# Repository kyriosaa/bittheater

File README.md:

# BitTheater: A Miniature Animation Showcase

BitTheater is a compact, tactile device that brings your custom animations to life, displaying up to 4 unique animations in a sleek, pocket-sized design.

Special thanks to [PCBWay](https://www.pcbway.com/) for their sponsorship and high-quality PCB prototyping service! Their PCBs are very high quality with many options to choose from and I got my order shipped to me within 3 days. Check them out if you want a custom PCB for your own project.

🎥 Demo Videos 🎥
- [Prototype](https://youtu.be/qVx4EneCoxs)
- [v1.0 PCB](https://youtu.be/kq-y1wTctfI)

## Features

- **Custom Animations -** Includes up to 4 custom animations on a 16x2 LCD screen
- **Tactile Controls -** Uses two tactile push buttons for a satisfying click on every button press
- **Compact Design -** The device is built on a small perfboard, allowing components to be neatly soldered for a compact and pocket-sized design.

## Hardware Components

- **Arduino Nano -** Microcontroller
- **SC162A3 -** 16x2 LCD Display
- **Push Buttons -** Buttons
- **220Ω Resistors -** Pull-down resistors for push buttons

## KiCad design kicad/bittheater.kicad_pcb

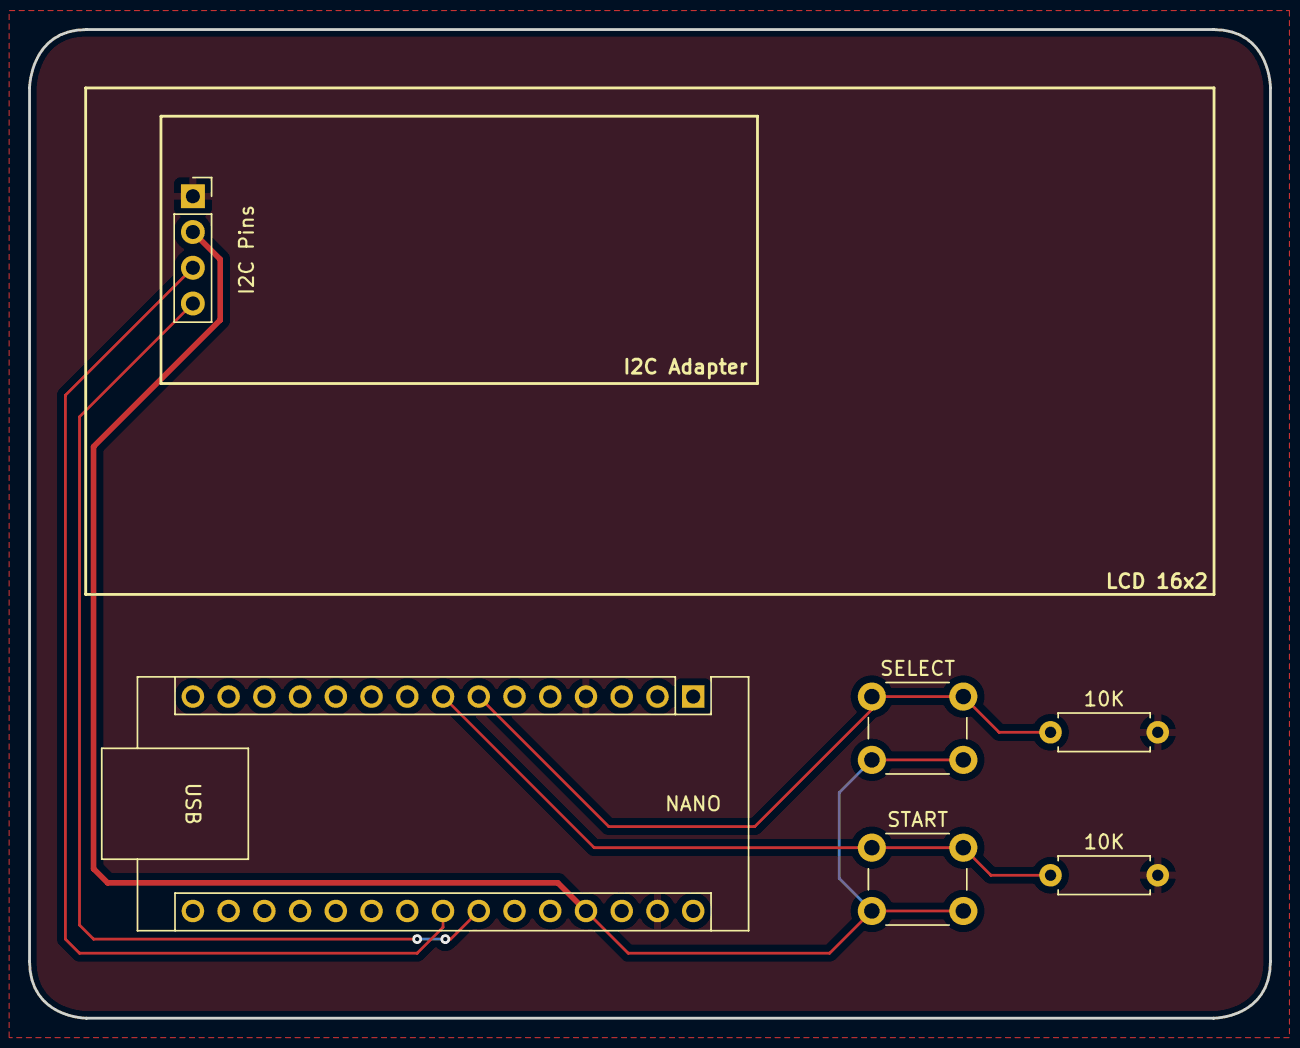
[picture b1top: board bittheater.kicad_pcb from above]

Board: 4 copper layers, 88.2 x 70.3 mm, 7 parts (1 on the bottom side), 6 nets.

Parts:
10K, 10K#2: 10K; R_Axial_DIN0207_L6.3mm_D2.5mm_P7.62mm_Horizontal
Ditto: LOGO
I2C Pins: LCD16x2_I2C_Header; PinSocket_1x04_P2.54mm_Vertical
NANO: Arduino_Nano_v3.x; Arduino_Nano
SELECT: SW_Push; SW_PUSH_6mm
START: SW_Push; SW_PUSH_6mm

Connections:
+5V: I2C Pins.2 (VCC), NANO.27 (+5V), SELECT.2, START.2
GND: 10K.2, 10K#2.2, I2C Pins.1 (GND), NANO.4 (GND), NANO.29 (GND)
unnamed: I2C Pins.3 (SDA), NANO.23 (A4)
unnamed: I2C Pins.4 (SCL), NANO.24 (A5)
unnamed: 10K#2.1, NANO.7 (D4), SELECT.1
unnamed: 10K.1, NANO.8 (D5), START.1

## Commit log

2025-02-28 Update project name
2025-02-28 Update AnimateHelloWorld & AnimateBlocks
2025-03-01 Add AnimateJpGreeting & Improve code readability
2025-03-02 Add AnimateIntro & small animation fixes
2025-03-02 Update folder structure & Add pcb project files
2025-03-24 feature: added CRUMB design
2025-03-27 docs: added project images
2025-03-27 feature: update AnimateIntro.cpp
2025-03-27 docs: added README.md
2025-03-27 docs: updated README.md
2025-04-04 docs: updated image placement in README.md
2025-04-04 docs: updated hardware components in README.md
2025-04-30 docs: update image path in README.md
2025-04-30 docs: fix spacing issue in README.md
2025-05-07 docs: update hyperlink
2025-05-11 pcb: Added complete PCB file + gerbers
2025-05-22 pcb: update to v1.0
2025-05-22 docs: image update
2025-05-30 docs: update PCBWay sponsorship message
2025-08-04 update project description
2025-10-02 update documentation
